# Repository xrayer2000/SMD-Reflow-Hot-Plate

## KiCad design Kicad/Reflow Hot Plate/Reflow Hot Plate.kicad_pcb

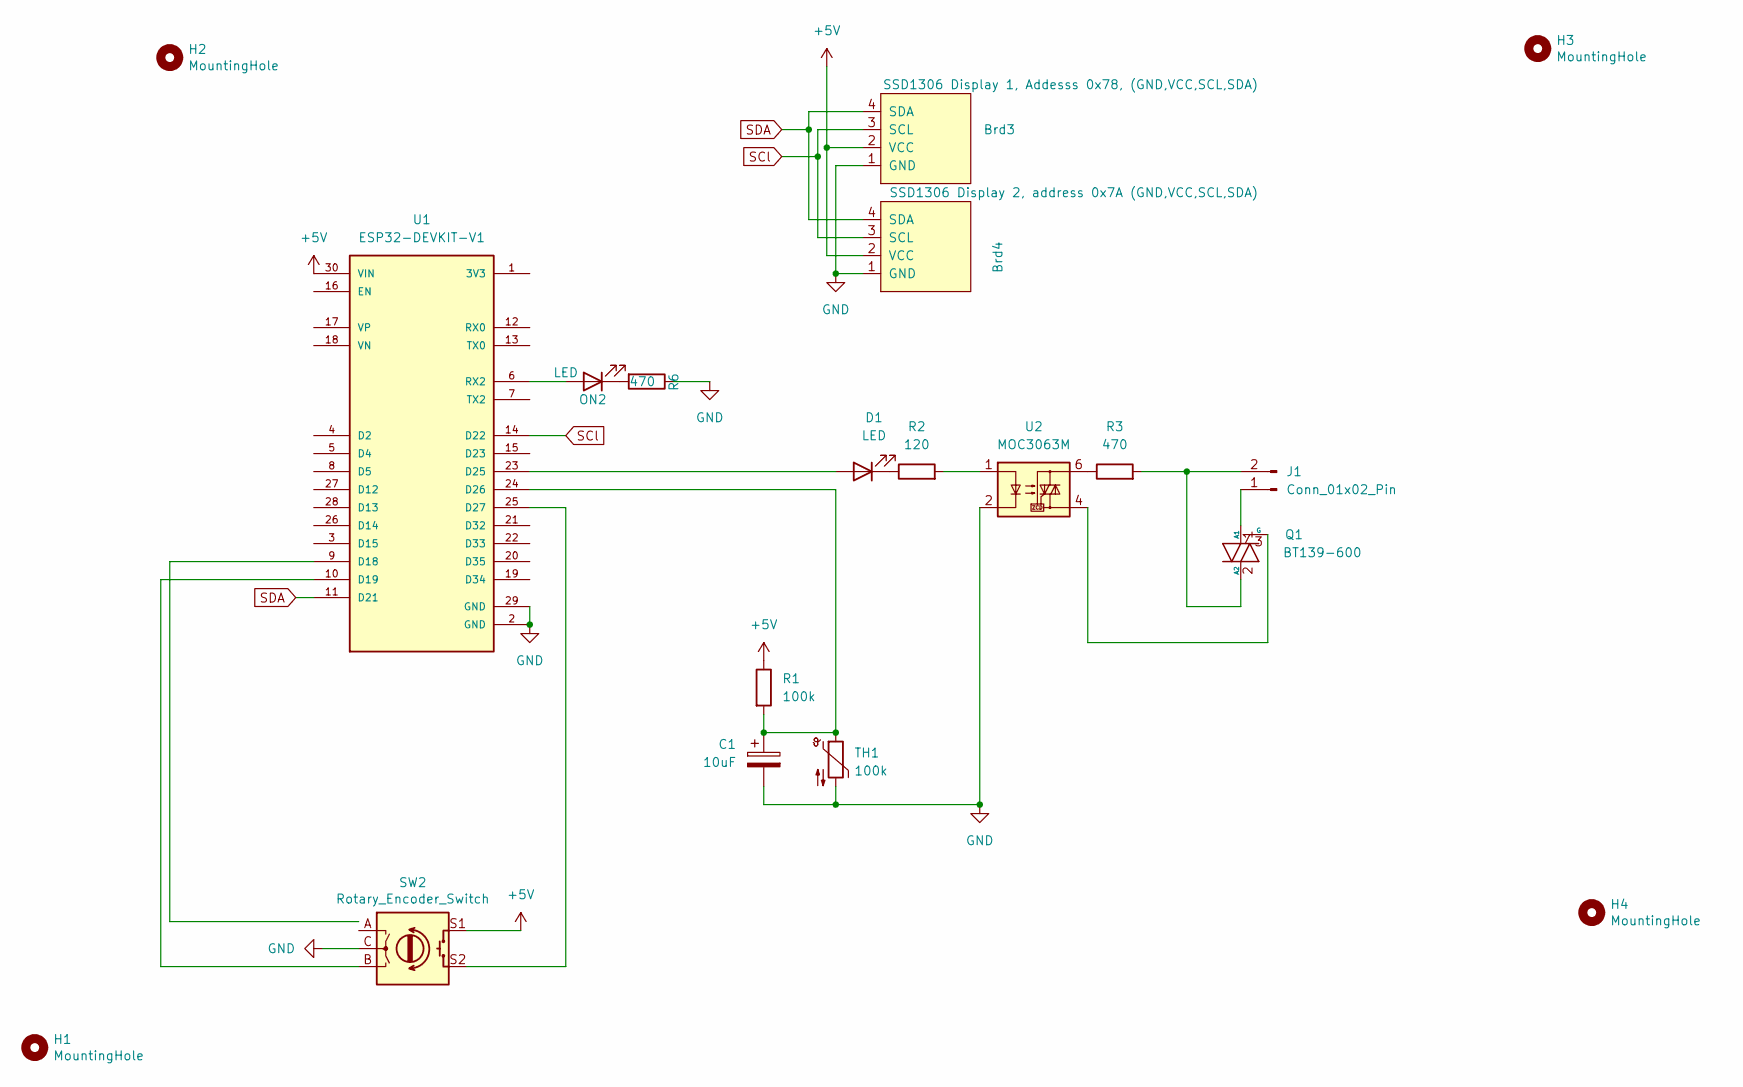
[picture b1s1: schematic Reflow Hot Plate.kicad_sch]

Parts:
Brd3: SSD1306 Display 1, Addesss 0x78, (GND,VCC,SCL,SDA); ssd1306_1.3''
Brd4: SSD1306 Display 2, address 0x7A (GND,VCC,SCL,SDA); ssd1306_1.3''
C1: 10uF; CP_Radial_D4.0mm_P2.00mm
D1: LED; LED_D3.0mm
H1, H2, H3, H4: MountingHole; MountingHole_3.2mm_M3_DIN965_Pad
J1: Conn_01x02_Pin; TerminalBlock_Phoenix_MPT-0,5-2-2.54_1x02_P2.54mm_Horizontal
ON2: LED; LED_D3.0mm
Q1: BT139-600; TO-220-3_Vertical
R1: 100k; R_Axial_DIN0207_L6.3mm_D2.5mm_P7.62mm_Horizontal
R2: 120; R_Axial_DIN0207_L6.3mm_D2.5mm_P7.62mm_Horizontal
R3, R6: 470; R_Axial_DIN0207_L6.3mm_D2.5mm_P7.62mm_Horizontal
SW2: Rotary_Encoder_Switch; RotaryEncoder_Alps_EC11E-Switch_Vertical_H20mm
TH1: 100k; JST_XH_B2B-XH-A_1x02_P2.50mm_Vertical
U1: ESP32-DEVKIT-V1; MODULE_ESP32_DEVKIT_V1; PARTREV N/A
U2: MOC3063M; DIP-6_W7.62mm_Socket

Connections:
+5V: Brd3.2 (VCC), Brd4.2 (VCC), R1.1, SW2.S1, U1.30 (VIN)
GND: Brd3.1 (GND), Brd4.1 (GND), C1.2, R6.1, SW2.C, TH1.2, U1.2 (GND), U1.29 (GND), U2.2
unnamed: D1.2 (A), U1.23 (D25)
unnamed: D1.1 (K), R2.1
unnamed: J1.1, Q1.1 (A1)
unnamed: J1.2, Q1.2 (A2), R3.2
unnamed: ON2.2 (A), U1.6 (RX2)
unnamed: ON2.1 (K), R6.2
unnamed: Q1.3 (G), U2.4
unnamed: R2.2, U2.1
unnamed: R3.1, U2.6
unnamed: SW2.B, U1.10 (D19)
unnamed: C1.1, R1.2, TH1.1, U1.24 (D26)
unnamed: SW2.S2, U1.25 (D27)
SCl: Brd3.3 (SCL), Brd4.3 (SCL), U1.14 (D22)
SDA: Brd3.4 (SDA), Brd4.4 (SDA), U1.11 (D21)

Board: 2 copper layers, 19 parts (0 on the bottom side), 16 nets, no tracks yet.

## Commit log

2025-06-23 added kicad and falstad
2025-06-23 modified main.ino
2025-06-23 added Reflow hot plate map
